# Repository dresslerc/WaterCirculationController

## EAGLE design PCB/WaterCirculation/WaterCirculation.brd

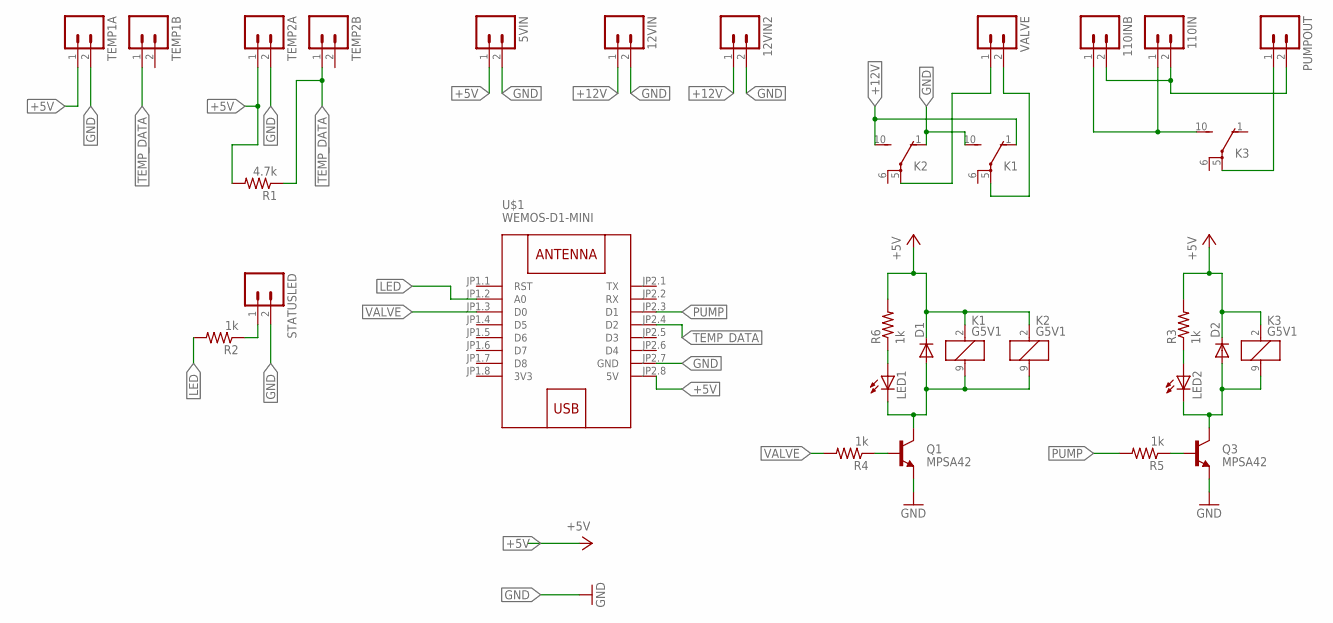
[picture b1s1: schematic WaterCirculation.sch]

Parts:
5VIN, 12VIN, 12VIN2, 110IN, 110INB: M023.5MM; SCREWTERMINAL-3.5MM-2
D1, D2: DIODE-SOD123; SOD123
K1, K2, K3: G5V1
LED1, LED2: LEDCHIP-LED0805; CHIP-LED0805
PUMPOUT: M023.5MM; SCREWTERMINAL-3.5MM-2
Q1, Q3: MPSA42; SOT23-3
R1: 4.7k; R0805
R2, R3, R4, R5, R6: 1k; R0805
STATUSLED: M023.5MM; SCREWTERMINAL-3.5MM-2
TEMP1A, TEMP1B, TEMP2A, TEMP2B: M023.5MM; SCREWTERMINAL-3.5MM-2
U$1: WEMOS-D1-MINI
VALVE: M023.5MM; SCREWTERMINAL-3.5MM-2

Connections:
3V3: U$1.JP1.8 (3V3)
+5V: 5VIN.1, D1.C, D2.C, K1.2 (1), K2.2 (1), K3.2 (1), R1.2, R3.2, R6.2, TEMP1A.1, TEMP2A.1, U$1.JP2.8 (5V)
+12V: 12VIN.1, 12VIN2.1, K1.1 (O), K2.10 (S)
GND: 5VIN.2, 12VIN.2, 12VIN2.2, K1.10 (S), K2.1 (O), Q1.2 (E), Q3.2 (E), STATUSLED.2, TEMP1A.2, TEMP2A.2, U$1.JP2.7 (GND)
LED: R2.2, U$1.JP1.2 (A0)
unnamed: Q1.1 (B), R4.1
unnamed: D1.A, K1.9 (2), K2.9 (2), LED1.C, Q1.3 (C)
unnamed: LED1.A, R6.1
unnamed: K2.5, VALVE.1
unnamed: K1.5, VALVE.2
unnamed: 110IN.2, 110INB.2, PUMPOUT.2
unnamed: D2.A, K3.9 (2), LED2.C, Q3.3 (C)
unnamed: LED2.A, R3.1
unnamed: Q3.1 (B), R5.1
unnamed: 110IN.1, 110INB.1, K3.10 (S)
unnamed: K3.5, PUMPOUT.1
unnamed: R2.1, STATUSLED.1
PUMP: R5.2, U$1.JP2.3 (D1)
TEMP_DATA: R1.1, TEMP1B.1, TEMP2B.1, U$1.JP2.4 (D2)
VALVE: R4.2, U$1.JP1.3 (D0)

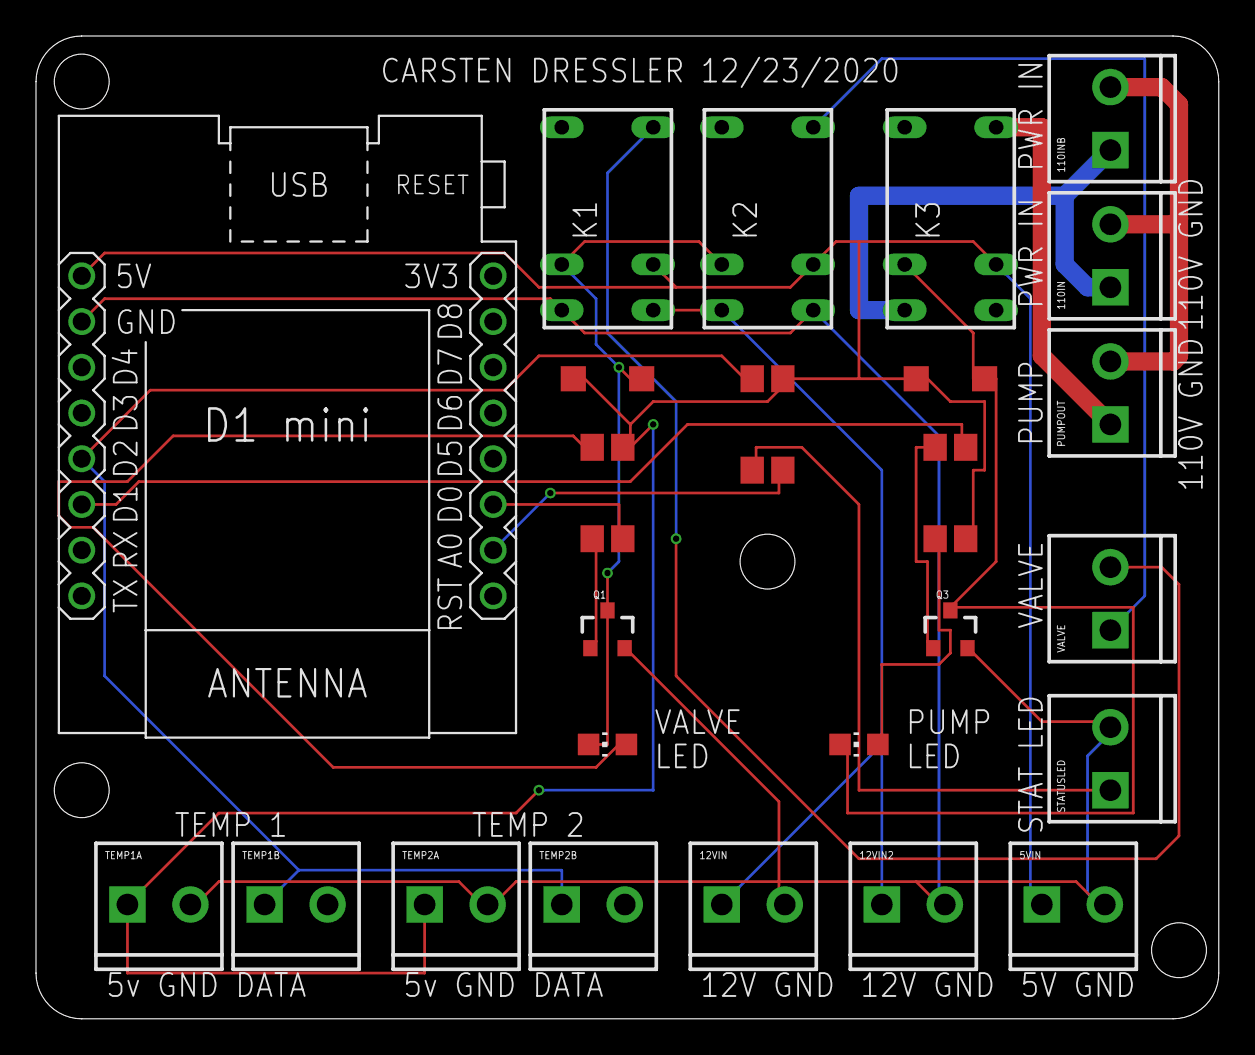
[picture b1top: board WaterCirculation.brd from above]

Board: 2 copper layers, 65.7 x 54.6 mm, 28 parts (0 on the bottom side), 19 nets.

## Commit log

2020-12-23 -Init Commit. No Board
    -Init Commit. No Board
2020-12-23 Board Layout
    Not finialized
2020-12-28 final layout
2020-12-30 OSH Park Release

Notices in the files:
parts and their libraries:
SparkFun-Connectors: Licensing: Creative Commons ShareAlike 4.0 International - https://creativecommons.org/licenses/by-sa/4.0
diy-modules: Released under the Creative Commons Attribution 4.0 International License: http://creativecommons.org/licenses/by/4.0
